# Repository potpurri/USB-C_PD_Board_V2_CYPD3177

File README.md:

# USB Type-C PD Voltage and Current Selection PCB

This PCB is designed to provide selectable output voltages and currents using the Infineon CYPD3177 USB Type-C port controller. It's equipped with switches that allow you to set the output voltage to 5V, 9V, 12V, 15V, or 20V and the current to 1A, 2A, 3A, 4A, or 5A.

## Features

- **USB Type-C Controller**: CYPD3177 with integrated fault protection and wide operating temperature range.
- **Selectable Output Voltage**: 5V, 9V, 12V, 15V, or 20V.
- **Selectable Output Current**: 1A, 2A, 3A, 4A, or 5A.
- **Compact Design**: Suitable for a variety of applications, including power tools, wearables, IoT devices, and more.
- **Turn ON Switch**: Switch to turn ON/OFF module.

## Voltage and Current Settings

The output voltage and current can be adjusted using switches on the PCB. SW1 is a SP4T switch and SW2 is a SPST switch. To use SW1, SW2 must be in position 1.  Refer to the table below for the settings:

| Voltage Setting | Output Voltage |
|-----------------|----------------|
| SW1-1           | 5V             |
| SW1-2           | 9V             |
| SW1-3           | 12V            |
| SW1-4           | 15V            |
| SW2-2           | 20V            |

| Current Setting | Output Current |
|-----------------|----------------|
| SW1-1           | 1A             |
| SW1-2           | 2A             |
| SW1-3           | 3A             |
| SW1-4           | 4A             |
| SW2-2           | 5A             |

## Images

### Schematic

### 3D Renderings
- Front View: 
- Front View without components: 
- Back View: 

### PCB
**4-Layer Stackup**: Signal Layer, GND Layer, Power Layer, Signal Layer
- All layers: 
- Front traces: 
- GND plane: 
- PWR plane: 
- Back traces: 

## Usage

1. **Output Voltage Selection**: Set the desired output voltage by configuring the appropriate switch on the PCB.
2. **Current Selection**: Set the desired current by adjusting the appropriate switch according to the table above.
3. **Connect Device**: Connect the device to the USB Type-C port.
4. **Power Input**: Provide power via the USB Type-C input, and the circuit will manage safe power delivery and maintain output stability.

---

This PCB is ideal for applications needing flexible power delivery with selectable voltage and current options.

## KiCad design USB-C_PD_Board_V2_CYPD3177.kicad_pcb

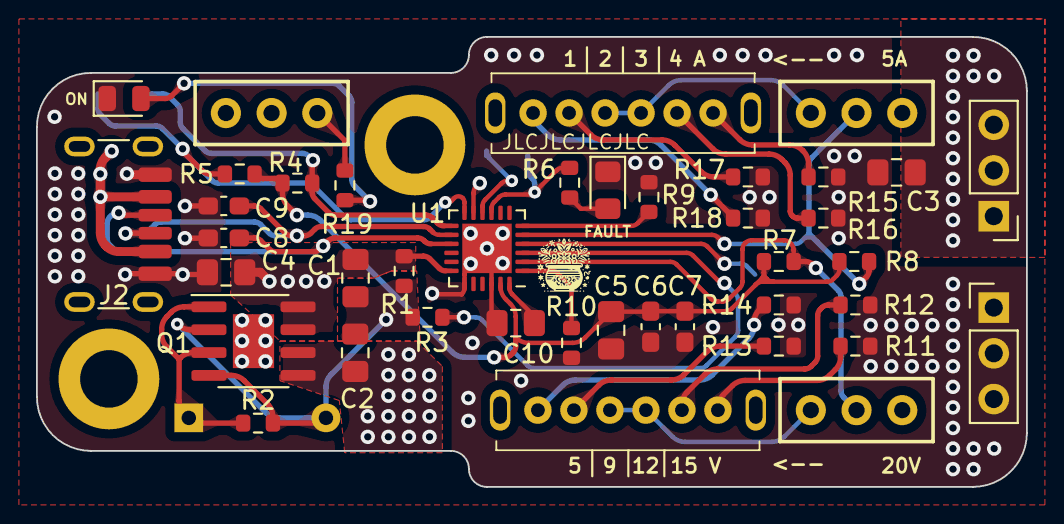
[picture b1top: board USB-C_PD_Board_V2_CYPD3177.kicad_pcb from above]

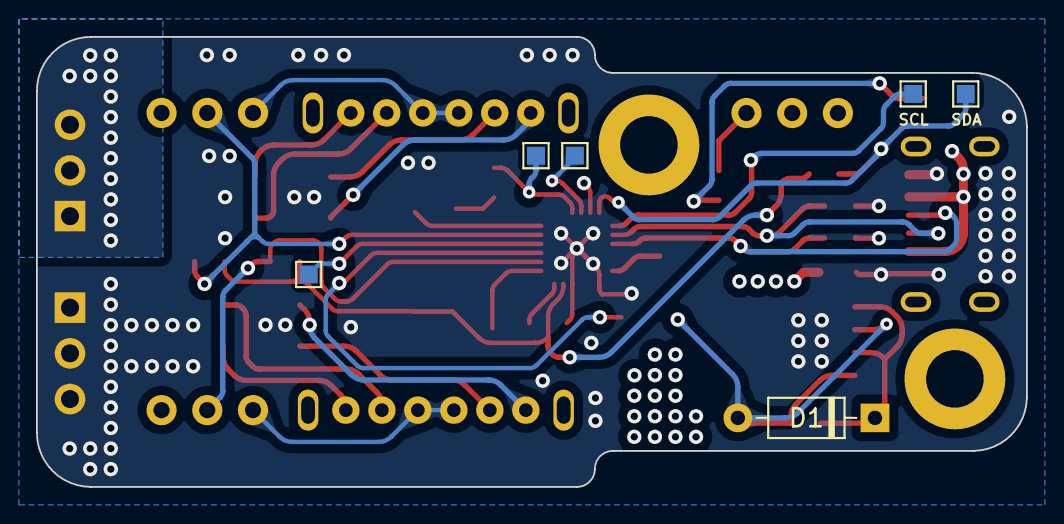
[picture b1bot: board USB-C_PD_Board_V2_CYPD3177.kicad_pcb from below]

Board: 4 copper layers, 55.0 x 25.0 mm, 49 parts (6 on the bottom side), 32 nets.

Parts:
C1, C2, C5, C10: 1u; C_0805_2012Metric_Pad1.18x1.45mm_HandSolder
C3, C4: 3u3; C_0805_2012Metric_Pad1.18x1.45mm_HandSolder
C6, C7: 100n; C_0603_1608Metric_Pad1.08x0.95mm_HandSolder
C8, C9: 390p; C_0603_1608Metric_Pad1.08x0.95mm_HandSolder
D1: D_Zener; D_DO-35_SOD27_P7.62mm_Horizontal
D2: LED; LED_0805_2012Metric_Pad1.15x1.40mm_HandSolder
D3: LED; LED_0805_2012Metric
H1, H2: MountingHole; MountingHole_3.2mm_M3_DIN965_Pad
J1, J4: Conn_01x03; PinHeader_1x03_P2.54mm_Vertical
J2: Type-C_6P; USB-C 6 Pin - Long pads
Q1: DMP3098LSD; SOIC-8-1EP_3.9x4.9mm_P1.27mm_EP2.29x3mm
R1, R15: 10k; R_0603_1608Metric
R2: 50K; R_0603_1608Metric
R3: 1K; R_0603_1608Metric
R4, R5, R12, R17: 2k4; R_0603_1608Metric
R6, R13, R18, R19: 1k; R_0603_1608Metric
R7, R8, R9, R10, R11, R16: 5k1; R_0603_1608Metric
R14: 0; R_0603_1608Metric
SW1, SW2, SW5: SW_SPDT; Schiebeschalter SS-12D00
SW3, SW4: SK-14D01-G 6
TP1, TP2, TP3, TP4, TP5: TestPoint; TestPoint_Pad_1.0x1.0mm
U1: CYPD3177-24LQ; QFN-24-1EP_4x4mm_P0.5mm_EP2.75x2.75mm

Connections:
+3V3: C5.1, C6.1, C7.1, R4.1, R5.1, R7.1, R8.1, U1.23 (VDDD)
+VSW: C2.1, C3.1, J1.1, J1.2, J1.3, Q1.5 (D), Q1.6 (G), U1.11 (VDC_OUT)
GND: C3.2, C4.2, C5.2, C6.2, C7.2, C8.2, C9.2, C10.2, D2.1 (K), D3.1 (K), J2.A12 (GND), J2.B12 (GND), J4.1, J4.2, J4.3, R9.2, R10.2, R11.2, R12.2, R13.2, R14.2, R15.2, R16.2, R17.2, R18.2, U1.19 (GND), U1.22 (GND), U1.25 (GND)
unnamed: C1.2, C2.2, D1.2 (A), Q1.2 (G), Q1.4 (G), R1.2, R2.2, R3.1
unnamed: D1.1 (K), Q1.1 (S), Q1.3 (S), R2.1
unnamed: D2.2 (A), R6.1
unnamed: D3.2 (A), R19.1
unnamed: C8.1, J2.A5 (CC1), U1.15 (CC1)
unnamed: C9.1, J2.B5 (CC2), U1.14 (CC2)
unnamed: R11.1, SW3.6
unnamed: R12.1, SW3.5
unnamed: R13.1, SW3.2
unnamed: R14.1, SW3.1
unnamed: R15.1, SW4.6
unnamed: R16.1, SW4.5
unnamed: R17.1, SW4.2
unnamed: R18.1, SW4.1
unnamed: SW1.1 (A), SW3.3, SW3.4
unnamed: R7.2, SW1.2 (B), U1.2 (VBUS_MAX)
unnamed: R8.2, SW2.2 (B), U1.5 (ISNK_COARSE)
unnamed: SW2.3 (C), SW4.3, SW4.4
unnamed: J2.A9 (VBUS), J2.B9 (VBUS), SW5.1 (A)
unnamed: R6.2, TP3.1, U1.9 (FAULT)
unnamed: TP2.1, U1.10 (FLIP)
unnamed: R4.2, TP5.1, U1.13 (HPI_SCL)
unnamed: R5.2, TP4.1, U1.12 (HPI_SDA)
unnamed: R9.1, U1.6 (ISNK_FINE)
unnamed: TP1.1, U1.4 (SAFE_PWR_EN)
unnamed: R3.2, U1.3 (VBUS_FET_EN)
unnamed: R10.1, U1.1 (VBUS_MIN)
unnamed: C10.1, U1.24 (VCCD)
VBUS: C1.1, C4.1, Q1.7 (D), Q1.8 (G), R1.1, R19.2, SW5.2 (B), SW5.3 (C), U1.18 (VBUS_IN)

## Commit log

2024-11-05 layout started
2024-11-06 started routing
2024-11-06 routing
2024-11-07 pcb layout and routing done!
2024-11-07 added images and readme
2024-11-07 Donegit add .
2024-11-07 Added jlc serial number silk screen
2024-11-21 added turn on/off switch, added diode to indicate on state
2024-11-21 missed .pro file?
2024-11-21 missed .pro file? (#2)
2024-11-21 added tear drops and curved traces
2024-12-16 added gerbers
